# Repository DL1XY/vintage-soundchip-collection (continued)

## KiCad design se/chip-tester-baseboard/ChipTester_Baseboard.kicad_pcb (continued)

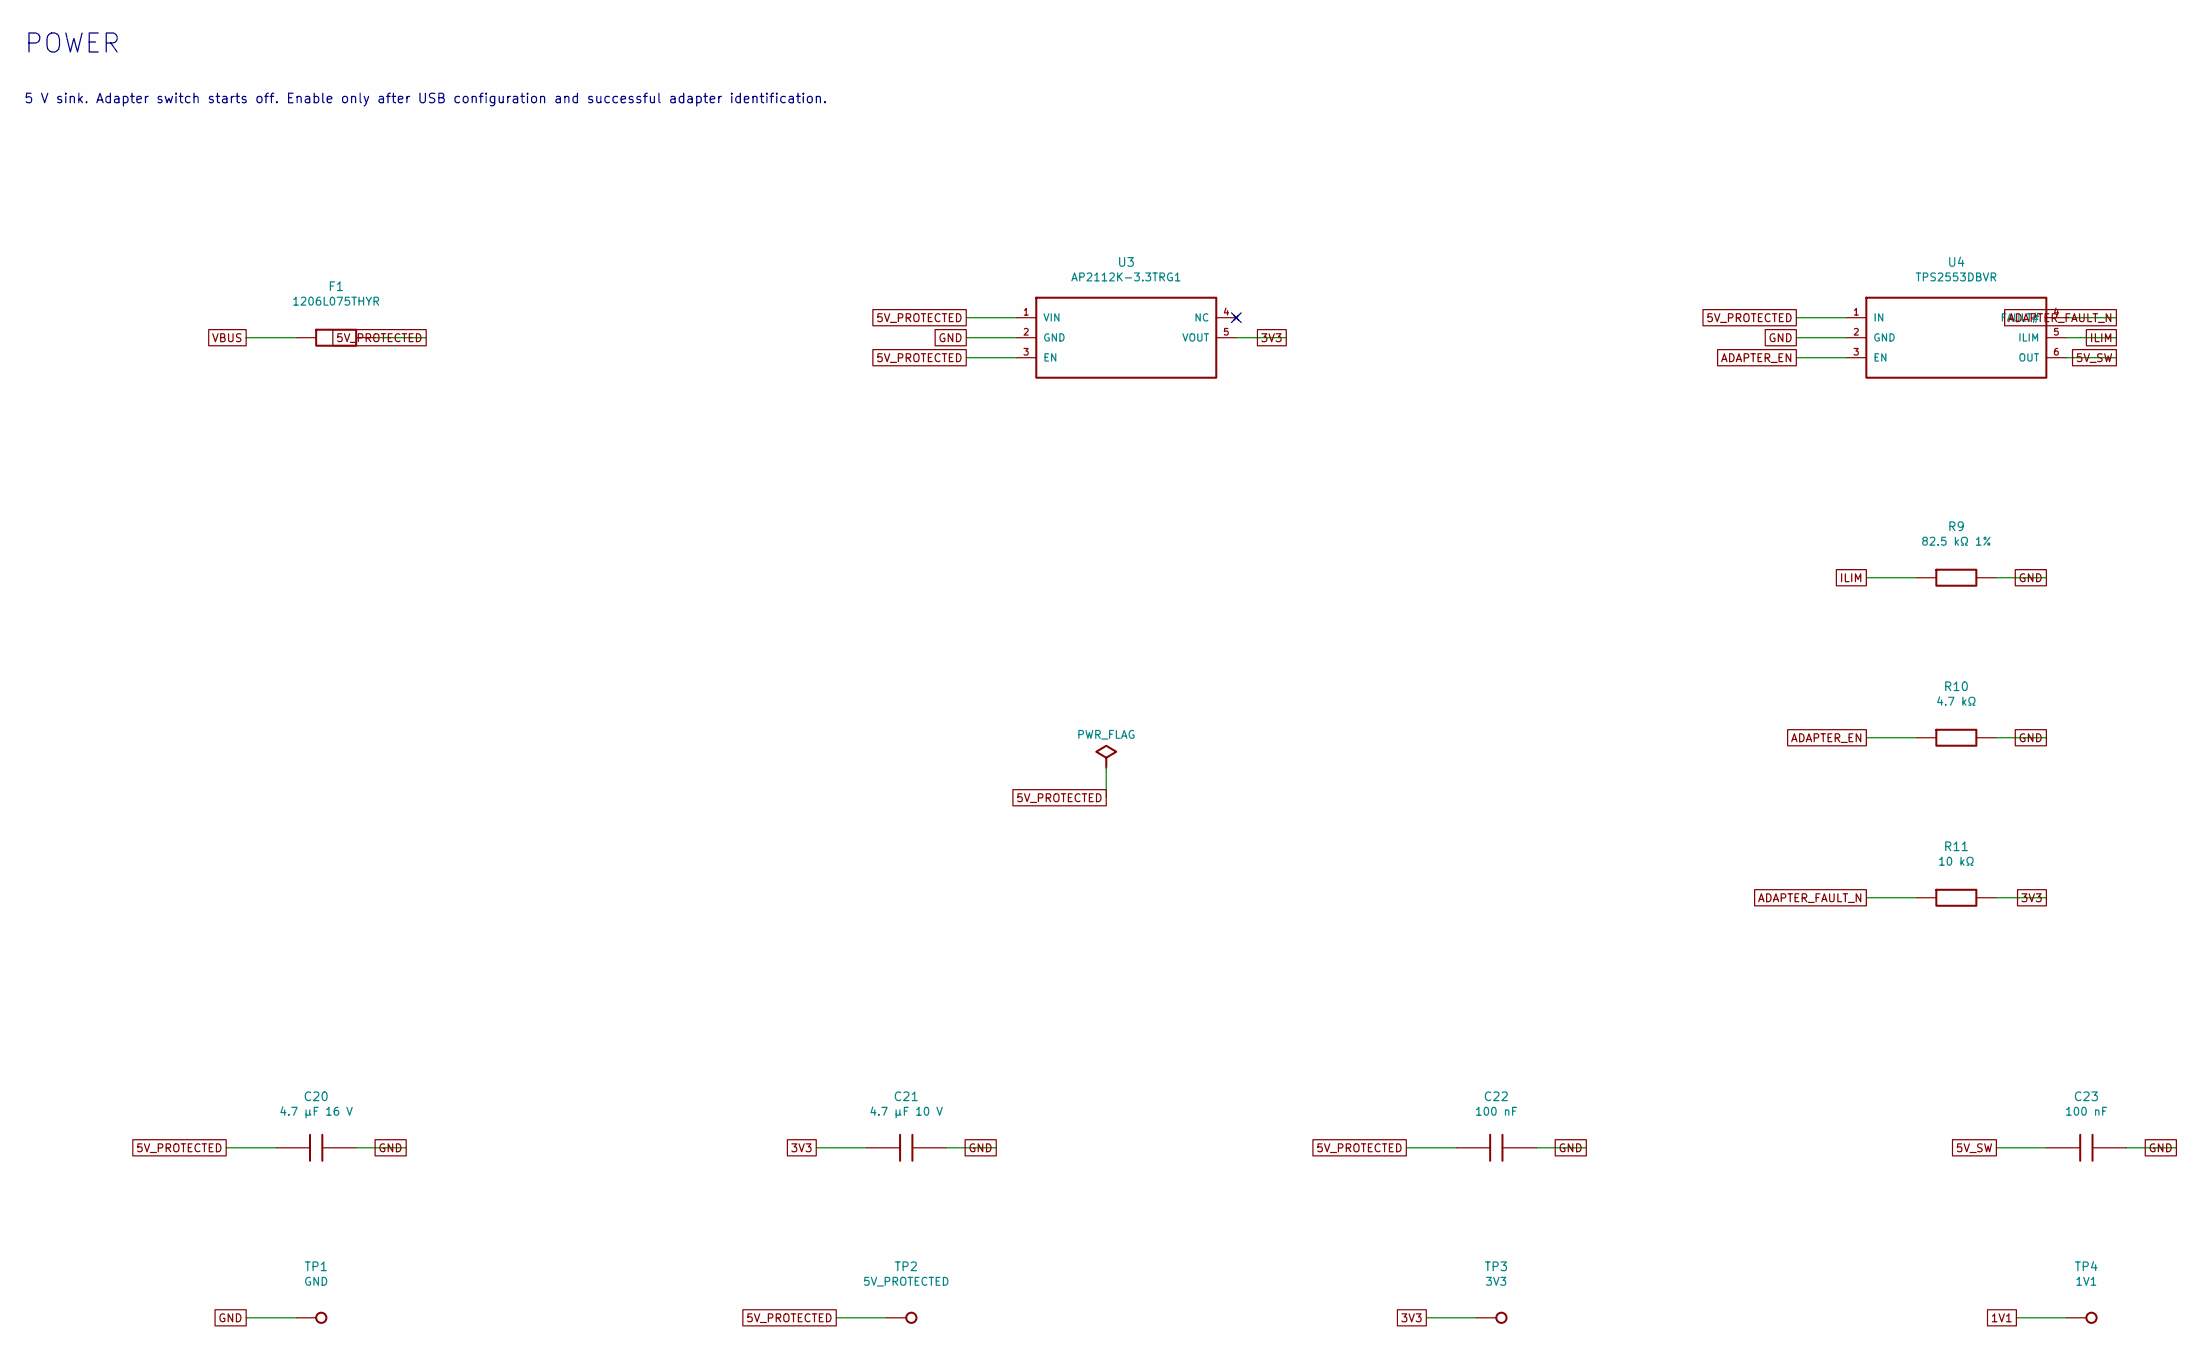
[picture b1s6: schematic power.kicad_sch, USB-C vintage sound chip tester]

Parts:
C20: 4.7 µF 16 V; C_0805
C21: 4.7 µF 10 V; C_0805
C22, C23: 100 nF; C_0805
F1: 1206L075THYR; F_1206
R9: 82.5 kΩ 1%; R_0805
R10: 4.7 kΩ; R_0805
R11: 10 kΩ; R_0805
TP1: GND; TestPoint_1mm
TP2: 5V_PROTECTED; TestPoint_1mm
TP3: 3V3; TestPoint_1mm
TP4: 1V1; TestPoint_1mm
U3: AP2112K-3.3TRG1; SOT23_5
U4: TPS2553DBVR; SOT23_6

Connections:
1V1: TP4.1; also elsewhere on the board
3V3: C21.1, R11.2, TP3.1, U3.5 (VOUT); also elsewhere on the board
5V_PROTECTED: C20.1, C22.1, F1.2, TP2.1, U3.1 (VIN), U3.3 (EN), U4.1 (IN); also elsewhere on the board
5V_SW: C23.1, U4.6 (OUT); also elsewhere on the board
ADAPTER_EN: R10.1, U4.3 (EN); also elsewhere on the board
ADAPTER_FAULT_N: R11.1, U4.4 (FAULT#); also elsewhere on the board
GND: C20.2, C21.2, C22.2, C23.2, R9.2, R10.2, TP1.1, U3.2 (GND), U4.2 (GND); also elsewhere on the board
ILIM: R9.1, U4.5 (ILIM)
VBUS: F1.1; also elsewhere on the board

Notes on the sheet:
5 V sink. Adapter switch starts off. Enable only after USB configuration and successful adapter identification.
POWER

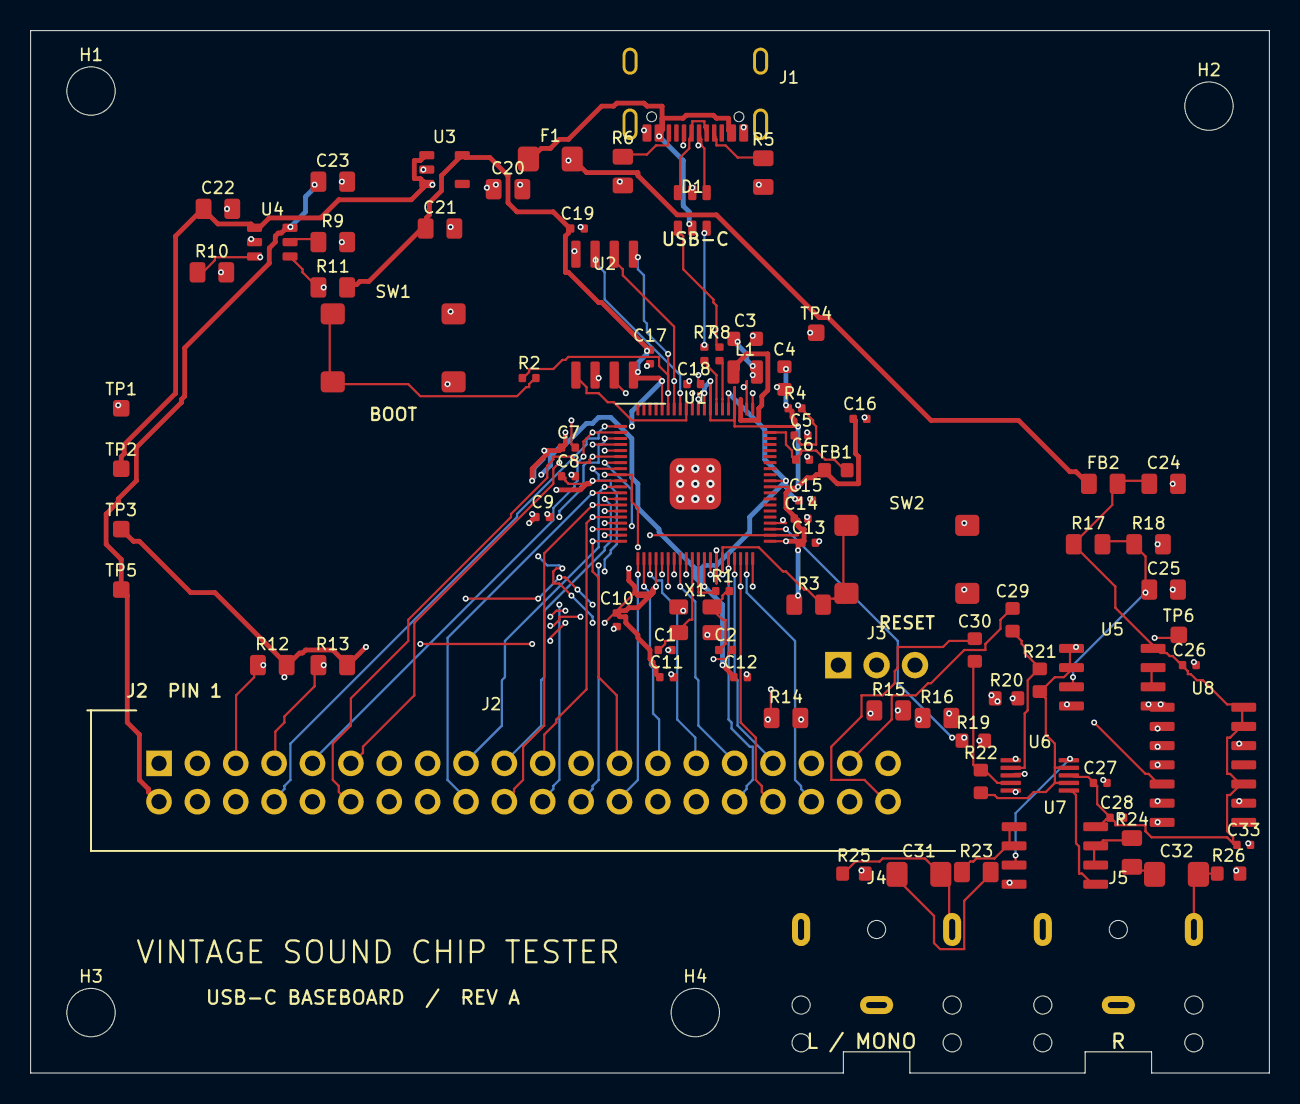
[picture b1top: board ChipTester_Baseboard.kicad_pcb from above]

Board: 4 copper layers, 82.0 x 69.0 mm, 90 parts (0 on the bottom side), 81 nets.

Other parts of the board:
H1, H2, H3, H4: M3; MountingHole_3.2mm

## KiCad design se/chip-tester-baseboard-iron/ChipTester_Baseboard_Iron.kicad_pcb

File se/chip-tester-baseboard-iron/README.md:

# USB-C sound chip tester baseboard · Rev B

Open [ChipTester_Baseboard_Iron.kicad_pro](ChipTester_Baseboard_Iron.kicad_pro) in KiCad 8 or newer. This revision is designed for assembly with a fine-tip soldering iron. The four-layer carrier measures 112 × 86 mm. [Rev A](../chip-tester-baseboard/README.md) uses a bare RP2350B and has its own layout.

## Assembly

1. Solder **D1 and U4** first. These are the two surface-mount parts on the carrier. Both have exposed SOT-23-6 leads at 0.95 mm pitch and extended solder pads. Tack one corner, align the remaining pins, then use flux and a fine tip to finish them. Inspect under magnification.
2. Install the axial resistors, radial capacitors, buttons, DIP sockets and through-hole connectors. The square pad and plus mark identify the positive side of the electrolytic capacitors. The ground zone uses thermal reliefs to make iron soldering easier.
3. Fit a **Pimoroni PGA2350 PIM722** on 2.54 mm pins. Align its A1 corner with the carrier's A1 mark. The layout uses the PIM722 pinout, including its USB data pins and 5 V supply input. Check alignment against the vendor drawing before soldering the full grid. [PGA2350 hardware documentation](https://shop.pimoroni.com/products/pga2350)
4. Fit an **Adafruit 4090** USB-C breakout, with its receptacle facing the edge marked USB-C. Use the 1×8 pin header and both mounting holes. Use spacers of the same height as the pin header support so plugging in the cable loads the hardware. Check that the plug seats fully. [Adafruit 4090 board files](https://github.com/adafruit/Adafruit-USB-C-Downstream-Breakout)

The module and USB-C breakout arrive with their fine-pitch components already soldered. The baseboard carries the USB data ESD clamp. The two USB series resistors are on the PGA2350.

## Parts for one baseboard

| Refs | Qty | Part |
| --- | ---: | --- |
| U1 | 1 | Pimoroni **PIM722** PGA2350 and 2.54 mm male pins for the 64-hole grid |
| J1 | 1 | Adafruit **4090** breakout, 1×8 2.54 mm pins and two M2.5 spacers with screws |
| D1, U4 | 1 each | **USBLC6-2SC6** ESD clamp and **TPS2553DBVR** current-limit switch |
| U5, U7 | 2 | **MCP6002-I/P** PDIP-8, with sockets if desired |
| U6 | 1 | **CD74HC4053E** PDIP-16, with socket if desired |
| F1 | 1 | **MF-R075** resettable fuse, 5.08 mm pitch |
| SW1, SW2 | 2 | **Omron B3F-1000** through-hole tactile switches |
| J2, J3 | 1 each | **WSL 40G** keyed 2×20 IDC header and 1×3 2.54 mm SWD header |
| J4, J5 | 2 | **SJ1-3523N** through-hole audio jacks |
| R1–R20 | 20 | Axial 1% resistors, 7.62 mm lead spacing. See schematic for values. |
| C1–C11 | 11 | Five 100 nF radial ceramics at 2.54 mm, two 1 µF film at 5.08 mm, one 47 µF and three 10 µF electrolytics with 5 mm body and 2 mm lead spacing |
| TP1–TP6 | 6 | 2.54 mm header pins or suitable wire loops |

Kamami listed PIM722 in stock and ships to Germany. Check availability before ordering the carrier. The older batch workbook prices Rev A. [Kamami PIM722](https://kamami.pl/en/base-boards-with-rp2040-and-rp235x/1199008-pga2350-mini-development-board-with-rp2350-microcontroller-769894025840.html) · [Kamami shipping](https://kamami.pl/en/content/6-delivery-and-payment)

Other sourcing references include [BerryBase for ADA4090](https://www.berrybase.de/en/adafruit-usb-type-c-breakout-board-downstream-connection), [Mouser Germany for CD74HC4053E](https://www.mouser.de/de/ProductDetail/Texas-Instruments/CD74HC4053E), and [Reichelt for WSL 40G](https://www.reichelt.de/de/de/shop/produkt/wannenstecker_40-polig_gerade-22834).

## Operation

The 40-pin adapter pinout and RP2350B firmware GPIO assignments match [Rev A](../chip-tester-baseboard/README.md#rp2350b-firmware-pin-assignments). The carrier uses the same clock and bus signals. USB CDC chip control and adapter profiles require firmware. To enter BOOTSEL, hold BOOTSEL while applying USB power. The RESET button grounds the module RUN pin.

The current-limited 5 V adapter supply defaults off. Allow adapter power only after USB configuration and identification. Budget the adapter's startup and steady-state current against the measured host current and minimum voltage at the chip. Switch off adapter power on suspend or fault, and disconnect USB before swapping.

Both outputs are AC-coupled and fixed gain. The analog section uses a filtered 3.3 V rail and an approximately 1.65 V midpoint. Start adapter calibration at **0.85 Vrms maximum** into a line input of 10 kΩ or higher, then measure clipping headroom. Mono adapters use L/MONO. Firmware can leave R muted independently.

## Verification before ordering

The schematic and board were checked independently for connector pinout, schematic-to-PCB net agreement and copper geometry. In KiCad, open the board, press **B** to fill the In1.Cu ground zone, then run native ERC and DRC and inspect the mountings. Native KiCad checks and hardware bring-up are pending. Confirm the USB-C data path in both cable orientations and measure adapter voltage, current limit, audio noise and startup transitions on the first build.

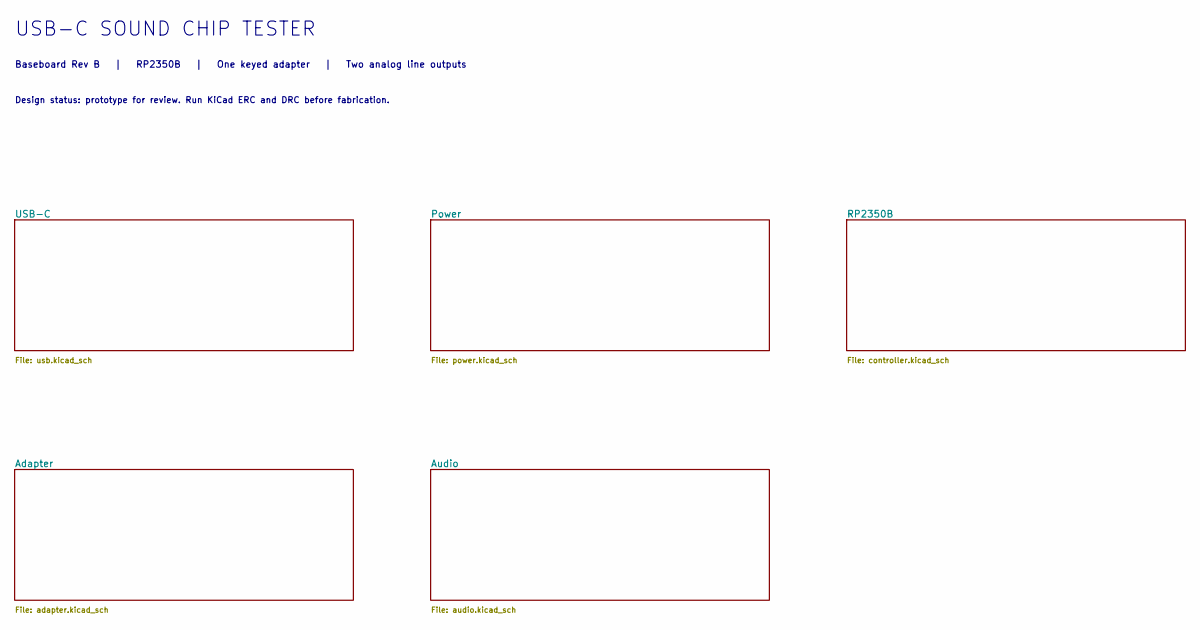
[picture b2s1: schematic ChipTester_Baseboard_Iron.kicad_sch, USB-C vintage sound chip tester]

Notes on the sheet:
Baseboard Rev B | RP2350B | One keyed adapter | Two analog line outputs
Design status: prototype for review. Run KiCad ERC and DRC before fabrication.
USB-C SOUND CHIP TESTER

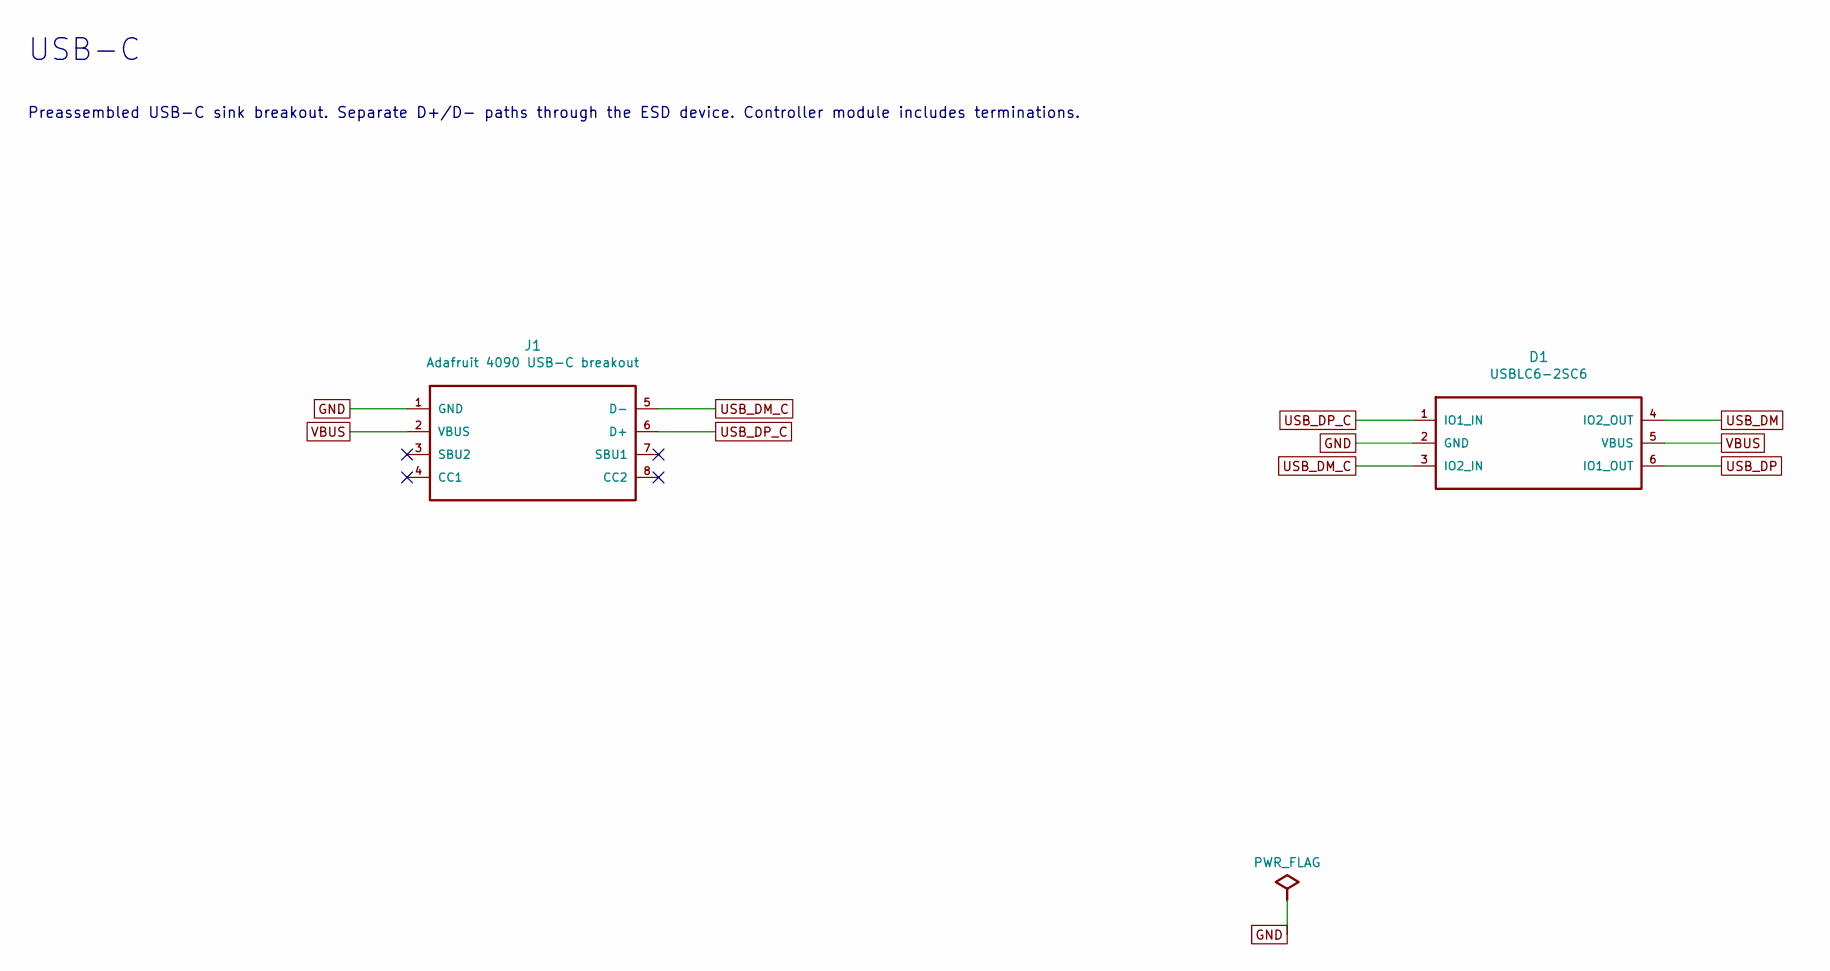
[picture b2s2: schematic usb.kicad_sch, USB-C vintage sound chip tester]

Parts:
D1: USBLC6-2SC6; SOT23_6_HandSolder_R90
J1: Adafruit 4090 USB-C breakout; Adafruit_4090_Header

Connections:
GND: D1.2 (GND), J1.1 (GND); also elsewhere on the board
USB_DM: D1.4 (IO2_OUT); also elsewhere on the board
USB_DM_C: D1.3 (IO2_IN), J1.5 (D-)
USB_DP: D1.6 (IO1_OUT); also elsewhere on the board
USB_DP_C: D1.1 (IO1_IN), J1.6 (D+)
VBUS: D1.5 (VBUS), J1.2 (VBUS); also elsewhere on the board

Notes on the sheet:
USB-C
Preassembled USB-C sink breakout. Separate D+/D- paths through the ESD device. Controller module includes terminations.

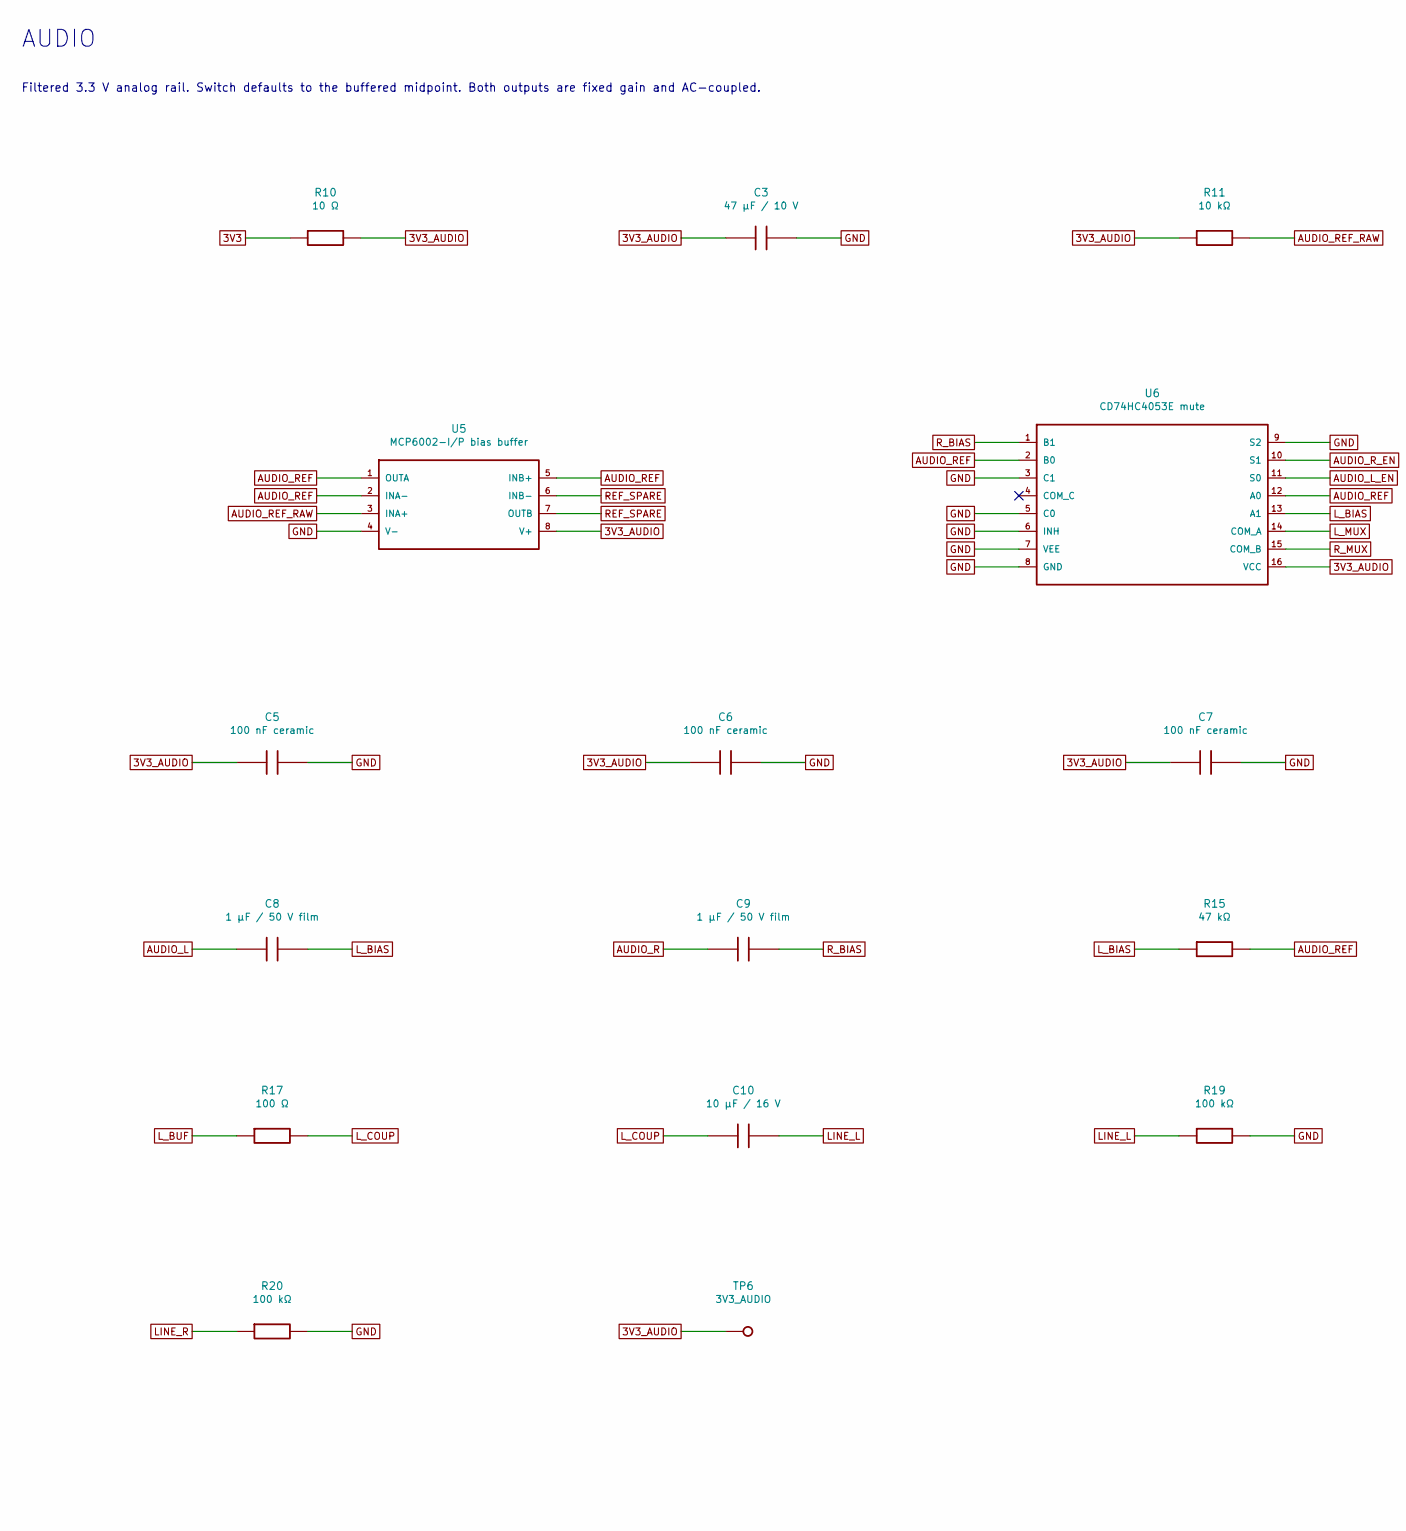
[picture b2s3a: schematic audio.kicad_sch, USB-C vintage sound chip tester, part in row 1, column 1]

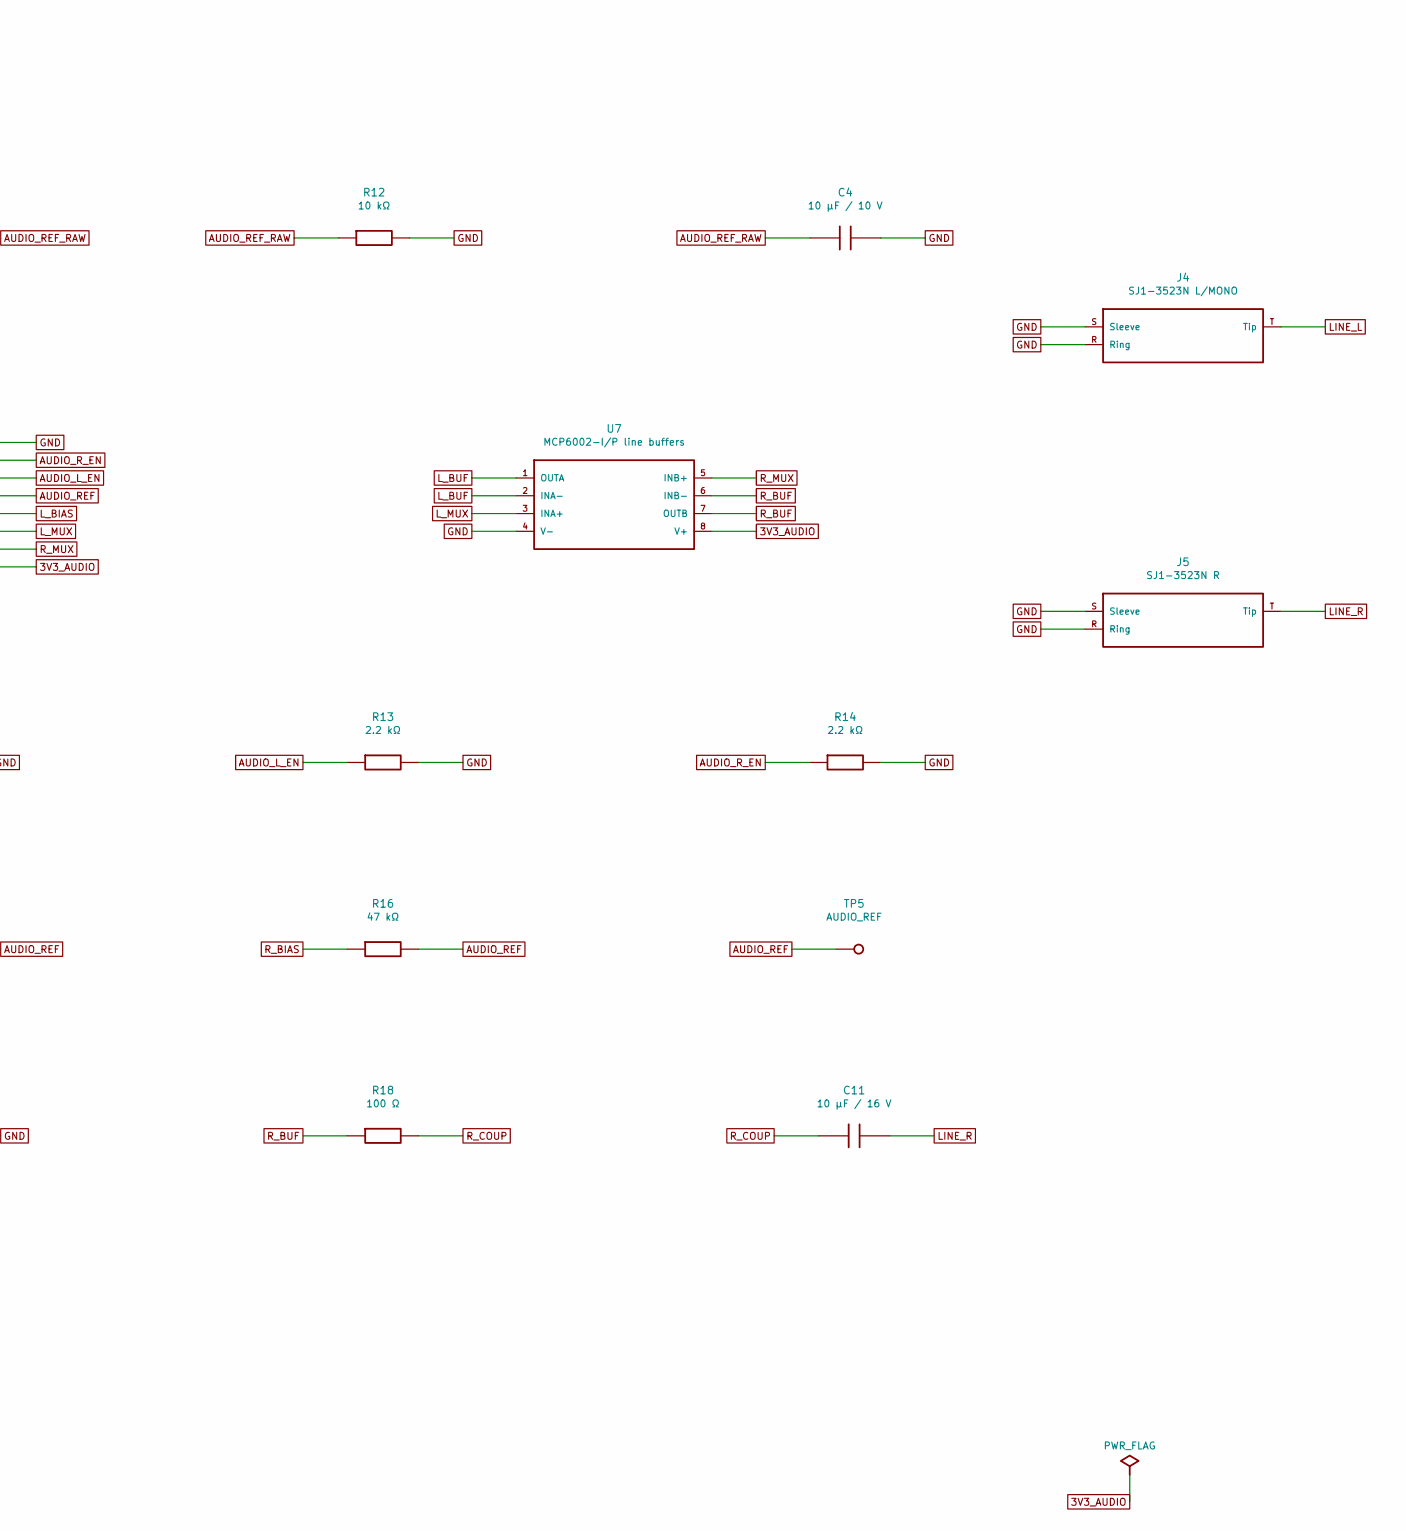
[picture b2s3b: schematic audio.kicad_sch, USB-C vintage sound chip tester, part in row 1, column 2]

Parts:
C3: 47 µF / 10 V; Radial_elect
C4: 10 µF / 10 V; Radial_elect
C5, C6, C7: 100 nF ceramic; Radial_cer
C8, C9: 1 µF / 50 V film; Radial_film_R90
C10, C11: 10 µF / 16 V; Radial_elect
J4: SJ1-3523N L/MONO; SJ1_3523N
J5: SJ1-3523N R; SJ1_3523N
R10: 10 Ω; Axial_7.62mm
R11, R12: 10 kΩ; Axial_7.62mm
R13, R14: 2.2 kΩ; Axial_7.62mm
R15, R16: 47 kΩ; Axial_7.62mm
R17, R18: 100 Ω; Axial_7.62mm
R19, R20: 100 kΩ; Axial_7.62mm
TP5: AUDIO_REF; TestPoint_THT
TP6: 3V3_AUDIO; TestPoint_THT
U5: MCP6002-I/P bias buffer; DIP8_7.62mm
U6: CD74HC4053E mute; DIP16_7.62mm
U7: MCP6002-I/P line buffers; DIP8_7.62mm

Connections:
3V3: R10.1; also elsewhere on the board
3V3_AUDIO: C3.1, C5.1, C6.1, C7.1, R10.2, R11.1, TP6.1, U5.8 (V+), U6.16 (VCC), U7.8 (V+)
AUDIO_L: C8.1; also elsewhere on the board
AUDIO_L_EN: R13.1, U6.11 (S0); also elsewhere on the board
AUDIO_R: C9.1; also elsewhere on the board
AUDIO_REF: R15.2, R16.2, TP5.1, U5.1 (OUTA), U5.2 (INA-), U5.5 (INB+), U6.2 (B0), U6.12 (A0)
AUDIO_REF_RAW: C4.1, R11.2, R12.1, U5.3 (INA+)
AUDIO_R_EN: R14.1, U6.10 (S1); also elsewhere on the board
GND: C3.2, C4.2, C5.2, C6.2, C7.2, J4.R (Ring), J4.S (Sleeve), J5.R (Ring), J5.S (Sleeve), R12.2, R13.2, R14.2, R19.2, R20.2, U5.4 (V-), U6.3 (C1), U6.5 (C0), U6.6 (INH), U6.7 (VEE), U6.8 (GND), U6.9 (S2), U7.4 (V-); also elsewhere on the board
LINE_L: C10.2, J4.T (Tip), R19.1
LINE_R: C11.2, J5.T (Tip), R20.1
L_BIAS: C8.2, R15.1, U6.13 (A1)
L_BUF: R17.1, U7.1 (OUTA), U7.2 (INA-)
L_COUP: C10.1, R17.2
L_MUX: U6.14 (COM_A), U7.3 (INA+)
REF_SPARE: U5.6 (INB-), U5.7 (OUTB)
R_BIAS: C9.2, R16.1, U6.1 (B1)
R_BUF: R18.1, U7.6 (INB-), U7.7 (OUTB)
R_COUP: C11.1, R18.2
R_MUX: U6.15 (COM_B), U7.5 (INB+)

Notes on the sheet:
AUDIO
Filtered 3.3 V analog rail. Switch defaults to the buffered midpoint. Both outputs are fixed gain and AC-coupled.

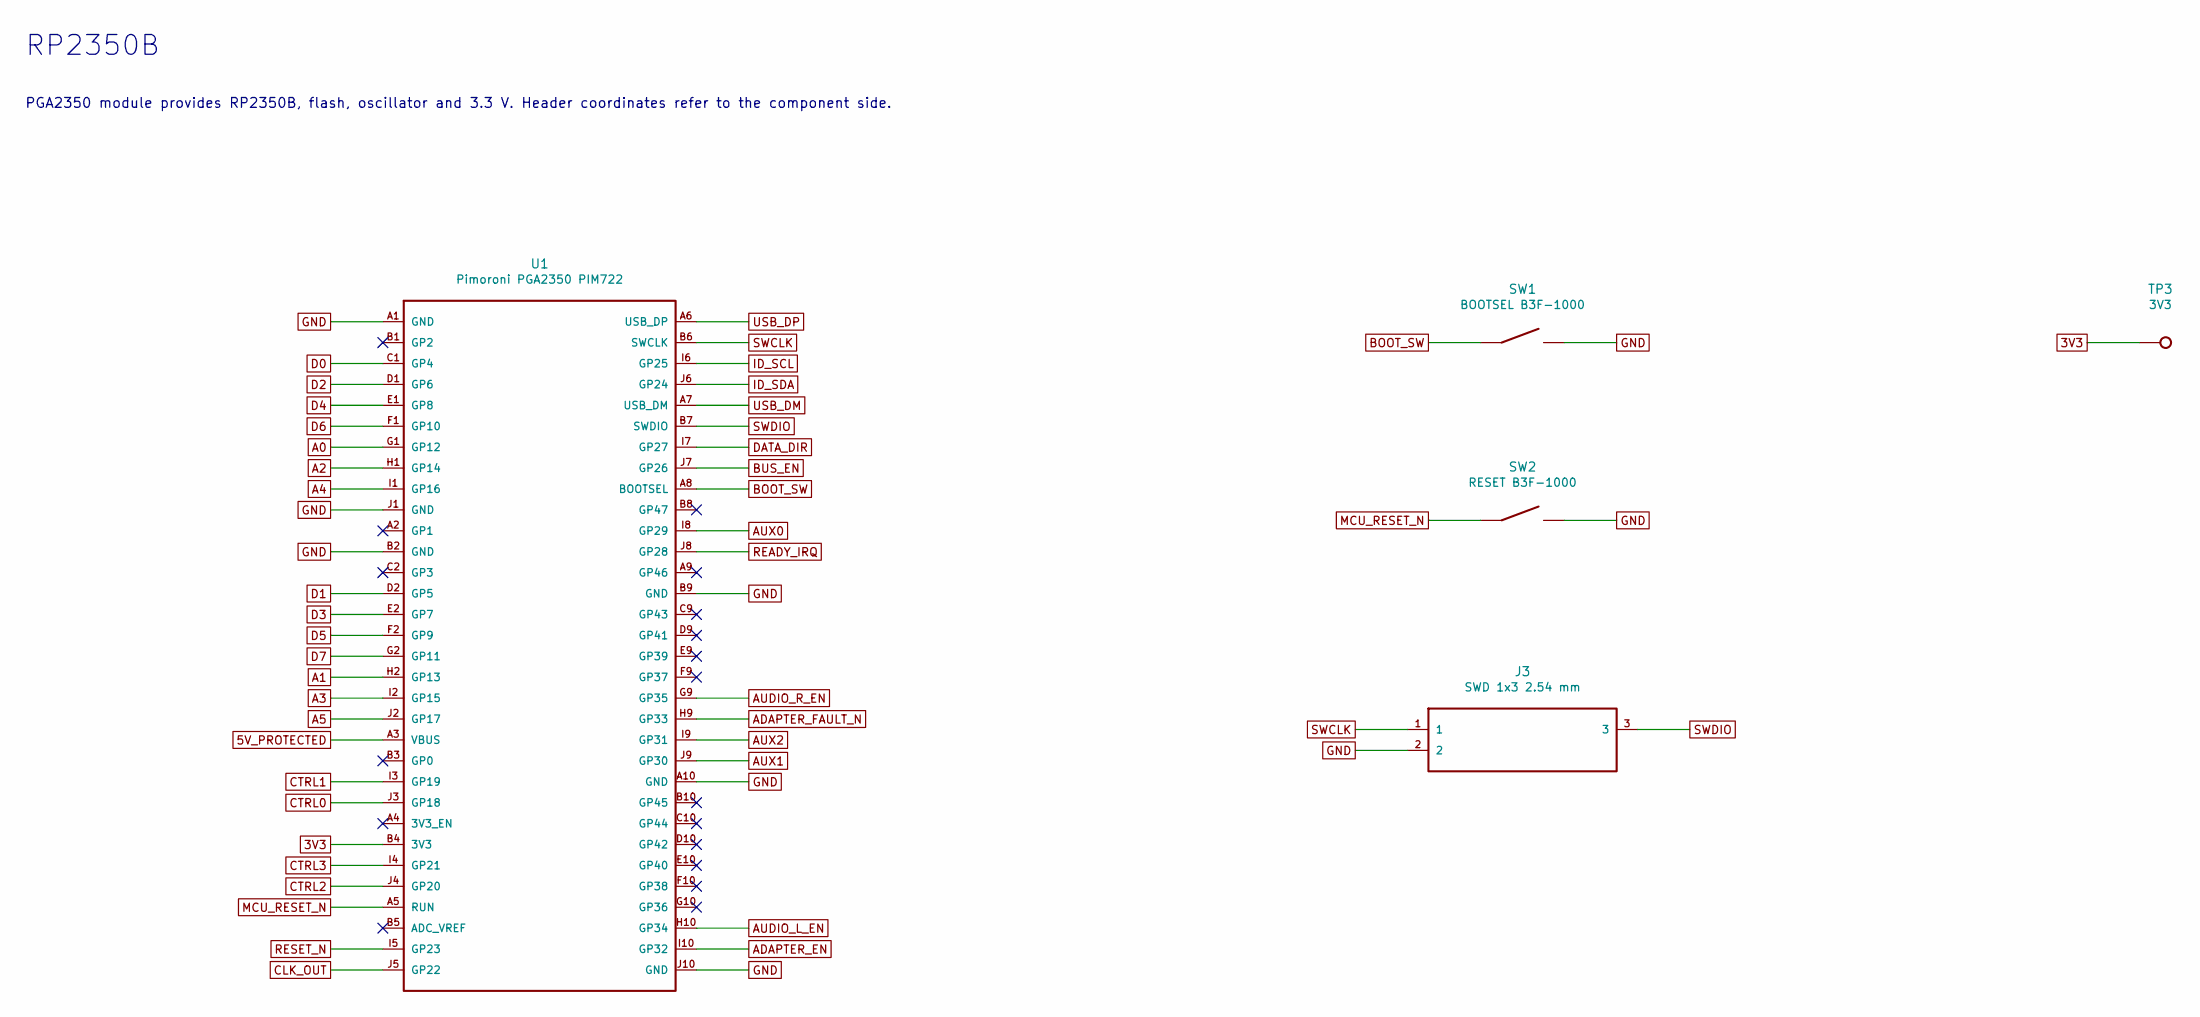
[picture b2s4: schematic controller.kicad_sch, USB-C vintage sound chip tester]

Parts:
J3: SWD 1x3 2.54 mm; Header_1x03
SW1: BOOTSEL B3F-1000; B3F_1000
SW2: RESET B3F-1000; B3F_1000
TP3: 3V3; TestPoint_THT
U1: Pimoroni PGA2350 PIM722; PGA2350_64_P2.54mm

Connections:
3V3: TP3.1, U1.B4 (3V3); also elsewhere on the board
5V_PROTECTED: U1.A3 (VBUS); also elsewhere on the board
A0: U1.G1 (GP12); also elsewhere on the board
A1: U1.H2 (GP13); also elsewhere on the board
A2: U1.H1 (GP14); also elsewhere on the board
A3: U1.I2 (GP15); also elsewhere on the board
A4: U1.I1 (GP16); also elsewhere on the board
A5: U1.J2 (GP17); also elsewhere on the board
ADAPTER_EN: U1.I10 (GP32); also elsewhere on the board
ADAPTER_FAULT_N: U1.H9 (GP33); also elsewhere on the board
AUDIO_L_EN: U1.H10 (GP34); also elsewhere on the board
AUDIO_R_EN: U1.G9 (GP35); also elsewhere on the board
AUX0: U1.I8 (GP29); also elsewhere on the board
AUX1: U1.J9 (GP30); also elsewhere on the board
AUX2: U1.I9 (GP31); also elsewhere on the board
BOOT_SW: SW1.1, U1.A8 (BOOTSEL)
BUS_EN: U1.J7 (GP26); also elsewhere on the board
CLK_OUT: U1.J5 (GP22); also elsewhere on the board
CTRL0: U1.J3 (GP18); also elsewhere on the board
CTRL1: U1.I3 (GP19); also elsewhere on the board
CTRL2: U1.J4 (GP20); also elsewhere on the board
CTRL3: U1.I4 (GP21); also elsewhere on the board
D0: U1.C1 (GP4); also elsewhere on the board
D1: U1.D2 (GP5); also elsewhere on the board
D2: U1.D1 (GP6); also elsewhere on the board
D3: U1.E2 (GP7); also elsewhere on the board
D4: U1.E1 (GP8); also elsewhere on the board
D5: U1.F2 (GP9); also elsewhere on the board
D6: U1.F1 (GP10); also elsewhere on the board
D7: U1.G2 (GP11); also elsewhere on the board
DATA_DIR: U1.I7 (GP27); also elsewhere on the board
GND: J3.2, SW1.2, SW2.2, U1.A1 (GND), U1.A10 (GND), U1.B2 (GND), U1.B9 (GND), U1.J1 (GND), U1.J10 (GND); also elsewhere on the board
ID_SCL: U1.I6 (GP25); also elsewhere on the board
ID_SDA: U1.J6 (GP24); also elsewhere on the board
MCU_RESET_N: SW2.1, U1.A5 (RUN)
READY_IRQ: U1.J8 (GP28); also elsewhere on the board
RESET_N: U1.I5 (GP23); also elsewhere on the board
SWCLK: J3.1, U1.B6 (SWCLK)
SWDIO: J3.3, U1.B7 (SWDIO)
USB_DM: U1.A7 (USB_DM); also elsewhere on the board
USB_DP: U1.A6 (USB_DP); also elsewhere on the board

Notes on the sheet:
RP2350B
PGA2350 module provides RP2350B, flash, oscillator and 3.3 V. Header coordinates refer to the component side.

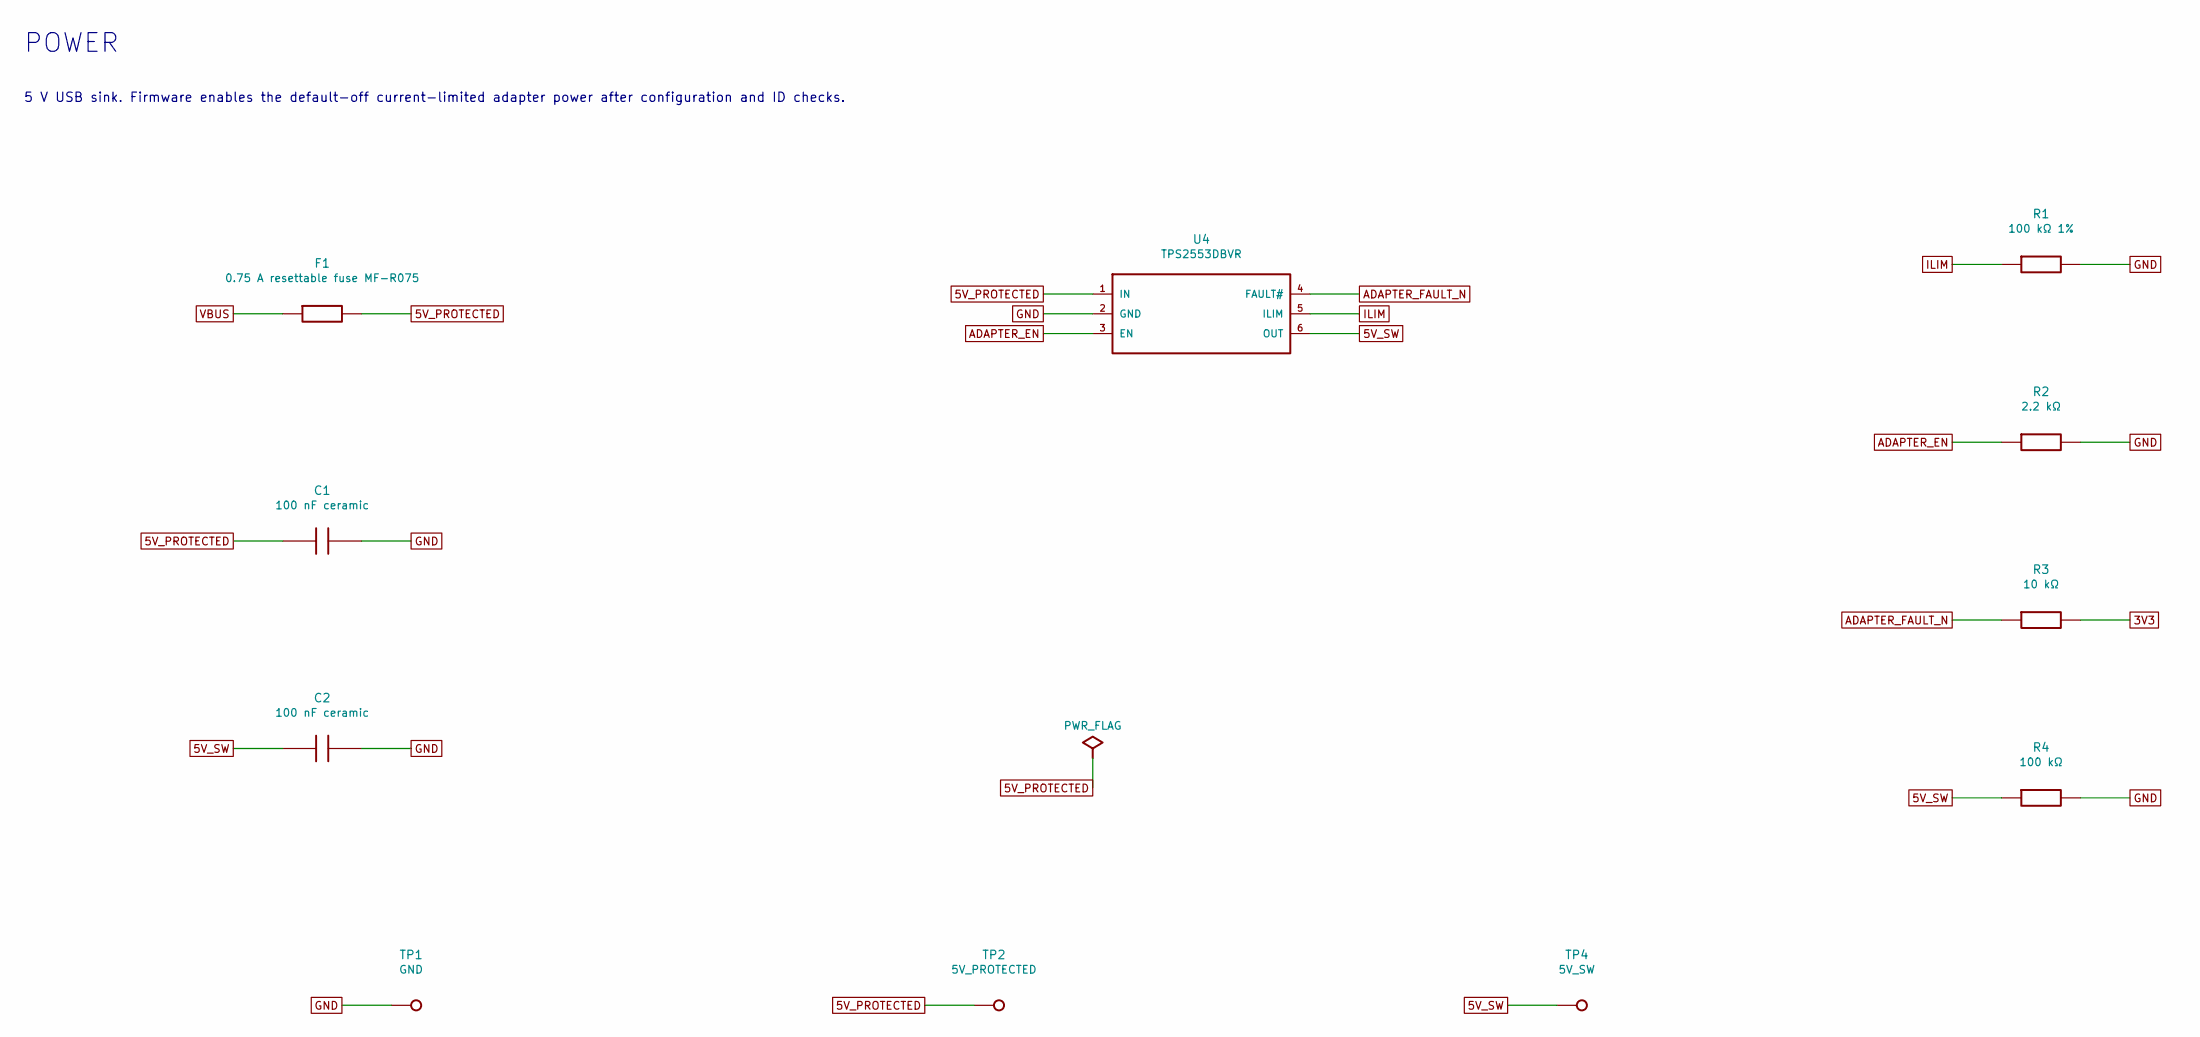
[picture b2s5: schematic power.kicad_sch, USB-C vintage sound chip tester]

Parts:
C1, C2: 100 nF ceramic; Radial_cer
F1: 0.75 A resettable fuse MF-R075; PTC_P5.08mm
R1: 100 kΩ 1%; Axial_7.62mm
R2: 2.2 kΩ; Axial_7.62mm
R3: 10 kΩ; Axial_7.62mm
R4: 100 kΩ; Axial_7.62mm
TP1: GND; TestPoint_THT
TP2: 5V_PROTECTED; TestPoint_THT
TP4: 5V_SW; TestPoint_THT
U4: TPS2553DBVR; SOT23_6_HandSolder

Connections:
3V3: R3.2; also elsewhere on the board
5V_PROTECTED: C1.1, F1.2, TP2.1, U4.1 (IN); also elsewhere on the board
5V_SW: C2.1, R4.1, TP4.1, U4.6 (OUT); also elsewhere on the board
ADAPTER_EN: R2.1, U4.3 (EN); also elsewhere on the board
ADAPTER_FAULT_N: R3.1, U4.4 (FAULT#); also elsewhere on the board
GND: C1.2, C2.2, R1.2, R2.2, R4.2, TP1.1, U4.2 (GND); also elsewhere on the board
ILIM: R1.1, U4.5 (ILIM)
VBUS: F1.1; also elsewhere on the board

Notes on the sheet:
POWER
5 V USB sink. Firmware enables the default-off current-limited adapter power after configuration and ID checks.
